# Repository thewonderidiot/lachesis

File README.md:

# Project Lachesis: AGC Core Rope Memory Readers

This repository contains all of the design files for safe, portable Block I and Block II Apollo Guidance Computer (AGC) core rope memory readers. For a detailed explanation of how it all works, check out [CuriousMarc's video featuring this project](https://www.youtube.com/watch?v=hckwxq8rnr0).

*Block 2 reader being used to dump the rope modules flown on Skylab-2 at the New Mexico Museum of Space History*

## Rope Safety Considerations

The rope readers are designed to be electrically and mechanically exactly identical to real AGCs from the point of view of the rope modules. Exact mechanical dimensions and interfacing circuits were copied from the original AGC engineering drawings, obtained from the National Archives. During bringup, all circuits are calibrated to the [original procurement specifications](https://github.com/thewonderidiot/lachesis/tree/main/docs). Connections to the rope modules are made using [replica Malco Mini-Wasp pins generously provided by Samtec](https://www.youtube.com/watch?v=ThOXgcOOA1M).

Additionally:
* A hotswap controller is used to switch all power being applied to the rope module. This controller monitors for overvoltage, undervoltage, and overcurrent, and will automatically cut power to the rope if limits are violated. The enable for this hotswap controller must be actively held high by the microcontroller in the FPGA for rope power to remain enabled.
* The microcontroller is configured with ~95ms watchdog timer. If the software gets stuck, the resulting watchdog reset will take all outputs low, thus cutting power to the rope.
* 250mA fuses have been added to the 450mA power filter circuits. These fuses are capable of withstanding the nominal 1-to-5-microsecond-long 450mA current pulses. However, if a driver gets stuck on for any reason, the associated fuse will blow within approximately 1 second. Calculations by thermal engineer friends suggest that, conservatively, a sustained 450mA on one of the drive wires would only be damaging to the rope module after 30 seconds.

## Block I Rework

The Sense & Driver Board requires a small amount of rework when used in the Block I configuration. While designing the board, I focused on getting Block II correct, while trying not to do anything that would outright prevent Block I compatibility. The only thing I didn't account for in the design is that from the perspective of the sense amplifiers, current on the sense lines actually flows in opposite directions between Block I and Block II. For Block II, the sense amplifiers pull the sense lines up to 14V, and a 128mA current sink is connected to the module select pin. Block I does not yet have this pin; instead, the sense lines were pulled *down* to 3V. Lacking a 3V rail capable of sinking the necessary current, the 128mA module select driver forms a perfectly suitable substitute. This can be accomplished by depopulating F9 and C11, and running a wire from pin A32 of the main connector to the + pad of C11.

## Rope Modules Archived

This is a non-exhaustive list of the rope modules that have been successfully read using the rope readers. Redundant reads of the same software from different physical modules are not listed.

<table>
  <tr>
    <th>Program</th>
    <th width=15%>Rope Part No.</th>
    <th>Source</th>
    <th width="50%">Notes</th>
  </tr>
  <tr>
    <td rowspan="4">Sunrise 69<br/>(Block I System Test)</td>
    <td>1003133-18</td>
    <td rowspan="2">Anonymous collector</td>
    <td rowspan="4">The 1003733-021 and 1003733-071 modules dumped both have one strand with a single bad diode, requiring parity correction.</td>
  </tr>
  <tr>
    <!--Sunrise 69-->
    <td>1003133-19</td>
    <!--Anonymous Collector-->
    <!--notes-->
  </tr>
  <tr>
    <!--Sunrise 69-->
    <td>1003733-021</td>
    <td>Larry McGlynn</td>
    <!--notes-->
  </tr> 
  <tr>
    <!--Sunrise 69-->
    <td>1003733-071</td>
    <td>Anonymous Collector</td>
    <!--notes-->
  </tr>
  <tr>
    <td rowspan="6">Corona 261<br/>(AS-202)</td>
    <td>1003733-171</td>
    <td rowspan="6">Jimmie Loocke</td>
    <td rowspan="6">All six modules were flown on AS-202. These modules contained a variety of failed or failing diodes, requiring parity correction for several strands. Notably, strands 21 and 23 each had 2 bad diodes, requiring the affected bits to be manually teased out by capturing waveforms of the cores flipping in both directions utilizing a differential probe. Additionally, 1003733-221 contained a broken core, resulting in the total loss of 8 words. Fortunately, these words turned out to be identical to the Apollo 4/6 software, Solarium 55.</td>
  </tr>
  <tr>
    <!--Corona 261-->
    <td>1003733-191</td>
    <!--Jimmie Loocke-->
    <!--notes-->
  </tr>
  <tr>
    <!--Corona 261-->
    <td>1003733-211</td>
    <!--Jimmie Loocke-->
    <!--notes-->
  </tr>
  <tr>
    <!--Corona 261-->
    <td>1003733-221</td>
    <!--Jimmie Loocke-->
    <!--notes-->
  </tr>
  <tr>
    <!--Corona 261-->
    <td>1003733-231</td>
    <!--Jimmie Loocke-->
    <!--notes-->
  </tr>
  <tr>
    <!--Corona 261-->
    <td>1003733-241</td>
    <!--Jimmie Loocke-->
    <!--notes-->
  </tr>
  <tr>
    <td rowspan="5">Sunspot ?<br/>(Early Apollo 1 release)</td>
    <td>1003733-251</td>
    <td rowspan="5">Dr. Nick Gessler</td>
    <td rowspan="5">Unfortunately, all modules have many failed diodes, precluding easy software recovery. Work to correct resulting errors is ongoing.</td>
  </tr>
  <tr>
    <!--Sunspot-->
    <td>1003733-261</td>
    <!--Dr. Nick Gessler-->
    <!--notes-->
  </tr>
  <tr>
    <!--Sunspot-->
    <td>1003733-281</td>
    <!--Dr. Nick Gessler-->
    <!--notes-->
  </tr>
  <tr>
    <!--Sunspot-->
    <td>1003733-291</td>
    <!--Dr. Nick Gessler-->
    <!--notes-->
  </tr>
  <tr>
    <!--Sunspot-->
    <td>1003733-311</td>
    <!--Dr. Nick Gessler-->
    <!--notes-->
  </tr>
  <tr>
    <td rowspan="5">Solarium 55<br/>(Apollo 4 and 6)</td>
    <td>1003733-461</td>
    <td rowspan="5">Jimmie Loocke</td>
    <td rowspan="5">All five modules were flown on Apollo 4.</td>
  </tr>
  <tr>
    <!--Solarium 55-->
    <td>1003733-471</td>
    <!--Jimmie Loocke-->
    <!--notes-->
  </tr>
  <tr>
    <!--Solarium 55-->
    <td>1003733-481</td>
    <!--Jimmie Loocke-->
    <!--notes-->
  </tr>
  <tr>
    <!--Solarium 55-->
    <td>1003733-511</td>
    <!--Jimmie Loocke-->
    <!--notes-->
  </tr>
  <tr>
    <!--Solarium 55-->
    <td>1003733-521</td>
    <!--Jimmie Loocke-->
    <!--notes-->
  </tr>
  <tr>
    <td>Aurora 85<br/>(Initial LM System Test)</td>
    <td>2003053-071</td>
    <td>Anonymous Collector</td>
    <td>Module B2 from Aurora 85. While module B1 of Aurora 88 is equivalent to Aurora 85, module B3 is not, so Aurora 85 has not yet been fully recovered.</td>
  </tr>
  <tr>
    <td rowspan="3">Aurora 88<br/>(Final LM System Test)</td>
    <td>2003972-011</td>
    <td rowspan="3">Steve Jurvetson</td>
    <td rowspan="3">Rope modules were installed in the guidance pallet flown on the F-8 in the Digital Fly-By-Wire program. The whereabouts of the actual DFBW modules are unknown.</td>
  </tr>
  <tr>
    <!--Aurora 88-->
    <td>2003972-091</td>
    <!--Steve Jurvetson-->
    <!--notes-->
  </tr>
  <tr>
    <!--Aurora 88-->
    <td>2003972-111</td>
    <!--Steve Jurvetson-->
    <!--notes-->
  </tr>
  <tr>
    <td>Sundial B<br/>(Initial CM System Test)</td>
    <td>2003053-151</td>
    <td>Anonymous Collector</td>
    <td>Module B2 from Sundial B. While module B1 of Sundial B is equivalent to Sundial D, module B3 is not, so Sundial B has not yet been fully recovered.</td>
  </tr>
  <tr>
    <td rowspan="2">Colossus 237<br/>(Apollo 8)</td>
    <td>2003972-541</td>
    <td rowspan="2">Anonymous Collector</td>
    <td rowspan="2">2003972-541 is marked "SCRAP UNIT" in red, but read without errors.</td>
  </tr>
  <tr>
    <!--Colossus 237-->
    <td>2003972-571</td>
    <!--Anonymous Collector-->
    <!--notes-->
  </tr>
  <tr>
    <td>Luminary 69<br/>(Apollo 10 LM)</td>
    <td>2003972-751</td>
    <td>Anonymous Collector</td>
    <td>First rope module successfully dumped.</td>
  </tr>
  <tr>
    <td rowspan="6">Comanche 67<br/>(Apollo 12 CM)</td>
    <td>2003972-1081</td>
    <td rowspan="6">Anonymous Collector</td>
    <td rowspan="6">Modules B1 through B4 were part of the flight spare set for Apollo 12. The high serial numbers for modules B5 and B6 suggest they were manufactured after the flight, for unknown reasons.</td>
  </tr>
  <tr>
    <!--Comanche 67-->
    <td>2003972-1091</td>
    <!--Anonymous Collector-->
    <!--notes-->
  </tr>
  <tr>
    <!--Comanche 67-->
    <td>2003972-1111</td>
    <!--Anonymous Collector-->
    <!--notes-->
  </tr>
  <tr>
    <!--Comanche 67-->
    <td>2003972-1121</td>
    <!--Anonymous Collector-->
    <!--notes-->
  </tr>
  <tr>
    <!--Comanche 67-->
    <td>2003972-1131</td>
    <!--Anonymous Collector-->
    <!--notes-->
  </tr>
  <tr>
    <!--Comanche 67-->
    <td>2003972-1141</td>
    <!--Anonymous Collector-->
    <!--notes-->
  </tr>
  <tr>
    <td>Comanche 72<br/>(Initial Apollo 13 CM release)</td>
    <td>2010802-021</td>
    <td>Anonymous Collector</td>
    <td>Module was initially slated fly on Apollo 13, but a bugfix in response to the Apollo 12 lightning strike requiring a re-release resulted in it remaining grounded.</td>
  </tr>
  <tr>
    <td>LM131 rev 1<br/>(Final Apollo 13 LM release)</td>
    <td>2010802-121</td>
    <td>Anonymous Collector</td>
    <td>Flight spare module. This is the only module different between LM131 rev 1 and Luminary 131 (for which scans of a program listing are available), so recovery of the software from this module resulted in the complete recovery of LM131 rev 1.</td>
  </tr>
  <tr>
    <td rowspan="6">Skylark 48<br/>(Skylab and ASTP CM)</td>
    <td>2010802-541</td>
    <td rowspan="6">New Mexico Museum of Space History</td>
    <td rowspan="6">All six modules were flown on the Skylab-2 mission, and possibly reflown on a later mission. Made possible by Chris Orwoll and Larry McGlynn.</td>
  </tr>
  <tr>
    <!--Skylark 48-->
    <td>2010802-551</td>
    <!--New Mexico Museum of Space History-->
    <!--notes-->
  </tr>
  <tr>
    <!--Skylark 48-->
    <td>2010802-561</td>
    <!--New Mexico Museum of Space History-->
    <!--notes-->
  </tr>
  <tr>
    <!--Skylark 48-->
    <td>2010802-571</td>
    <!--New Mexico Museum of Space History-->
    <!--notes-->
  </tr>
  <tr>
    <!--Skylark 48-->
    <td>2010802-581</td>
    <!--New Mexico Museum of Space History-->
    <!--notes-->
  </tr>
  <tr>
    <!--Skylark 48-->
    <td>2010802-591</td>
    <!--New Mexico Museum of Space History-->
    <!--notes-->
  </tr>
</table>

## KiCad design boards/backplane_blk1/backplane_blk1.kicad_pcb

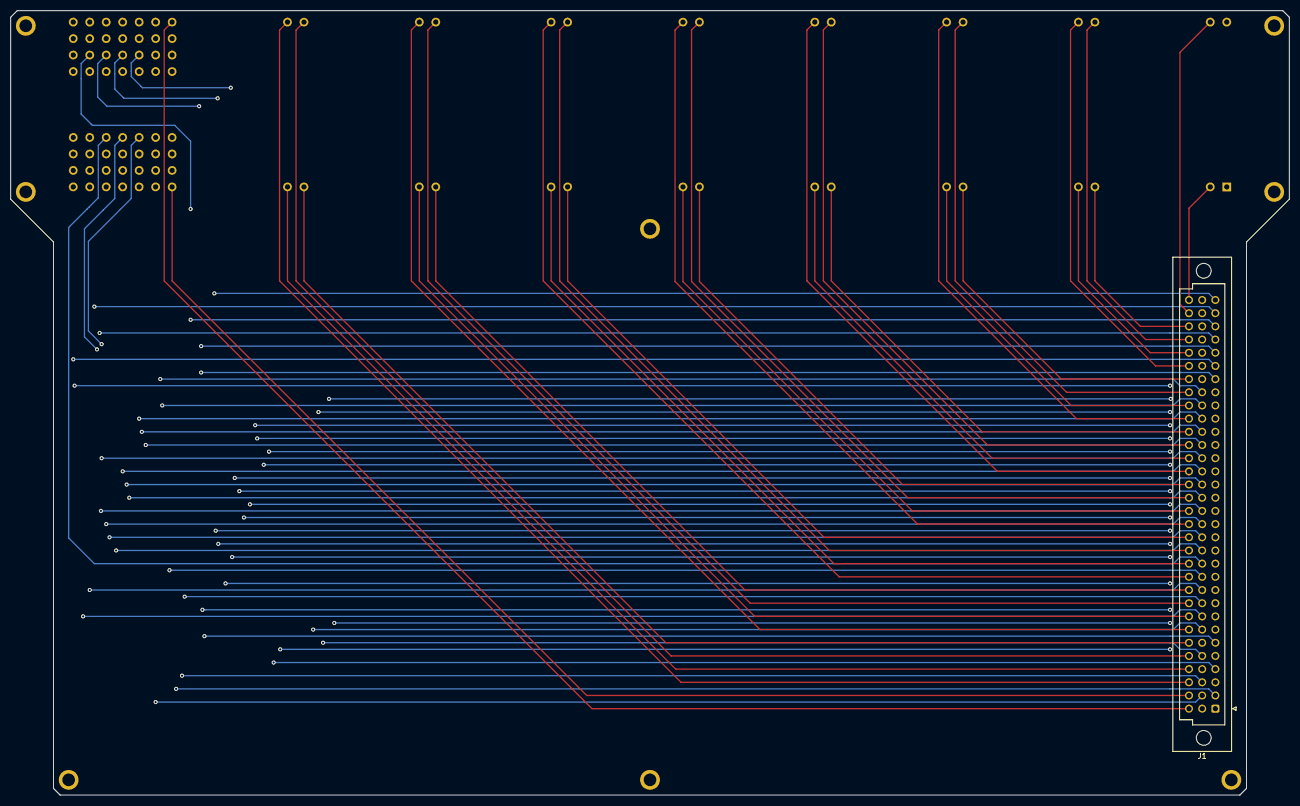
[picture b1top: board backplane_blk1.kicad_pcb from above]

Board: 4 copper layers, 246.4 x 151.1 mm, 10 parts (0 on the bottom side), 83 nets.

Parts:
H1, H2, H3, H4, H5, H6, H7, H8: MountingHole_Pad; MountingHole_No2_Pad
J1: DIN41612_03x32_C; DIN41612_R_3x32_Male_Vertical_THT
J2: Conn_04x22; Block1_Connector

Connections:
/GAR01: J1.c30, J2.5
/GAR02: J1.c28, J2.7
/GAR03: J1.c26, J2.9
/GAR04: J1.c24, J2.11
/GAR05: J1.c22, J2.13
/GAR06: J1.c20, J2.15
/GAR07: J1.c18, J2.17
/GAR08: J1.c16, J2.19
/GAR09: J1.c14, J2.21
/GAR10: J1.c12, J2.23
/GAR11: J1.c10, J2.25
/GAR12: J1.c8, J2.27
/GAR13: J1.c6, J2.29
/GAR14: J1.c4, J2.31
/GAR15: J1.c32, J2.3
/GAR16: J1.c2, J2.33
/GBR01: J1.c29, J2.6
/GBR02: J1.c27, J2.8
/GBR03: J1.c25, J2.10
/GBR04: J1.c23, J2.12
/GBR05: J1.c21, J2.14
/GBR06: J1.c19, J2.16
/GBR07: J1.c17, J2.18
/GBR08: J1.c15, J2.20
/GBR09: J1.c13, J2.22
/GBR10: J1.c11, J2.24
/GBR11: J1.c9, J2.26
/GBR12: J1.c7, J2.28
/GBR13: J1.c5, J2.30
/GBR14: J1.c3, J2.32
/GBR15: J1.c31, J2.4
/GBR16: J1.c1, J2.40
/R01CD: J1.b12, J2.68
/R01FD: J1.b13, J2.67
/R02CD: J1.b14, J2.66
/R02FD: J1.b15, J2.65
/R03CD: J1.b16, J2.60
/R03FD: J1.b17, J2.59
/R04CD: J1.b18, J2.58
/R04FD: J1.b19, J2.57
/R05CD: J1.b20, J2.52
/R05FD: J1.b21, J2.51
/R06CD: J1.b22, J2.50
/R06FD: J1.b23, J2.49
/R07CD: J1.b24, J2.43
/R07FD: J1.b25, J2.42
/RPCD: J1.b8, J2.74
/RPFD: J1.b10, J2.73
/RSTR1D: J1.b2, J2.41
/SDR00: J1.b11, J2.34
/SDR01: J1.a2, J2.35
/SDR02: J1.b9, J2.36
/SDR03: J1.b3, J2.44
/SDR04: J1.b7, J2.45
/SDR05: J1.a5, J2.37
/SDR06: J1.b5, J2.38
/SDR07: J1.a7, J2.39
/SETARN: J1.a29, J2.76
/SETBRN: J1.a25, J2.82
/SETCRN: J1.a32, J2.77
/SETDRN: J1.a28, J2.87
/X01CN: J1.a10, J2.69
/X01FN: J1.a12, J2.70
/X02CN: J1.a13, J2.71
/X02FN: J1.a14, J2.72
/X03CN: J1.a15, J2.61
/X03FN: J1.a16, J2.62
/X04CN: J1.a17, J2.63
/X04FN: J1.a18, J2.64
/X05CN: J1.a19, J2.53
/X05FN: J1.a20, J2.54
/X06CN: J1.a21, J2.55
/X06FN: J1.a22, J2.56
/X07CN: J1.a23, J2.46
/X07FN: J1.a24, J2.47
/XPCN: J1.a6, J2.79
/XPFN: J1.a8, J2.80
/XRST1N: J1.a4, J2.48
/XSETAD: J1.a31, J2.75
/XSETBD: J1.a27, J2.81
/XSETCD: J1.a30, J2.78
/XSETDD: J1.a26, J2.88
GND: H1.1, H2.1, H3.1, H4.1, H5.1, H6.1, H7.1, H8.1, J1.b26, J1.b27, J1.b28, J1.b29, J1.b30, J1.b31, J1.b32

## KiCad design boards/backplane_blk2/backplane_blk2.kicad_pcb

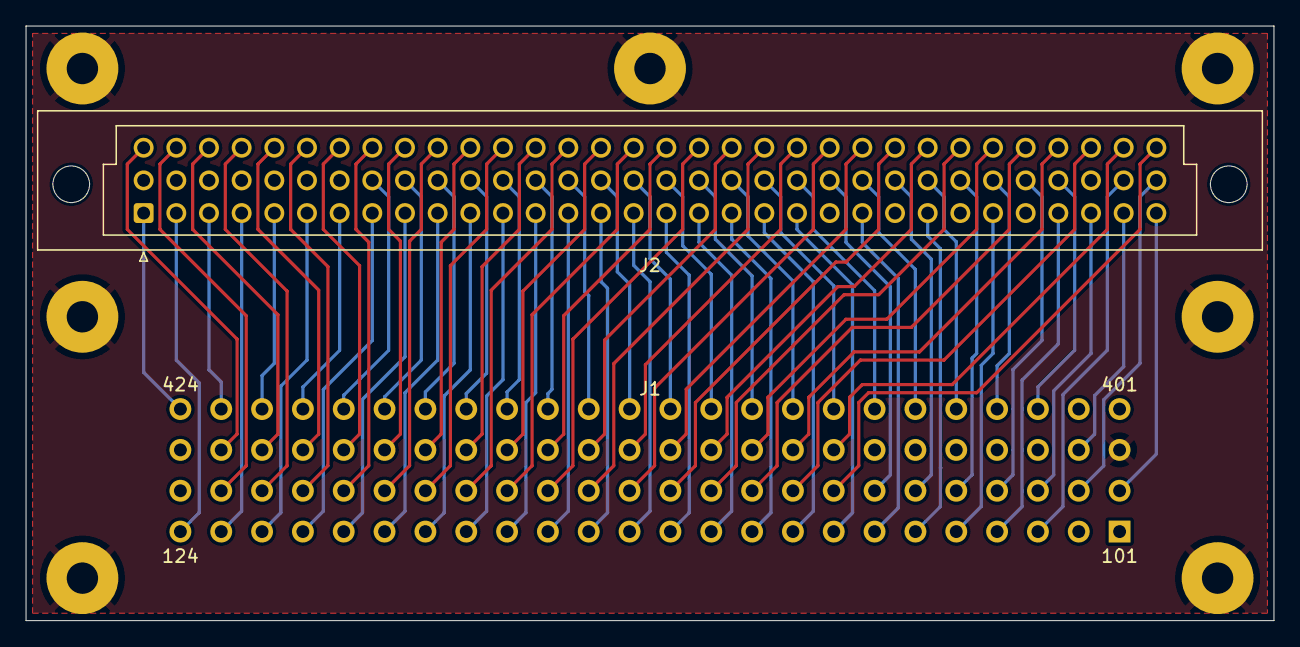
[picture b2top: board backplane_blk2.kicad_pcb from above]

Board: 4 copper layers, 97.0 x 46.2 mm, 9 parts (0 on the bottom side), 90 nets.

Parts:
H1, H2, H3, H4, H5, H6, H7: MountingHole_Pad; MountingHole_No2_0.22in_Pad
J1: Conn_04x24; Rope_Connector
J2: DIN41612_03x32_C; DIN41612_C_3x32_Female_Vertical_THT

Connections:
/GAR01: J1.322, J2.c3
/GAR02: J1.321, J2.c5
/GAR03: J1.320, J2.c7
/GAR04: J1.319, J2.c9
/GAR05: J1.318, J2.c11
/GAR06: J1.317, J2.c13
/GAR07: J1.316, J2.c15
/GAR08: J1.315, J2.c17
/GAR09: J1.314, J2.c19
/GAR10: J1.313, J2.c21
/GAR11: J1.312, J2.c23
/GAR12: J1.311, J2.c25
/GAR13: J1.310, J2.c27
/GAR14: J1.309, J2.c29
/GAR15: J1.323, J2.c1
/GAR16: J1.308, J2.c31
/GBR01: J1.222, J2.c4
/GBR02: J1.221, J2.c6
/GBR03: J1.220, J2.c8
/GBR04: J1.219, J2.c10
/GBR05: J1.218, J2.c12
/GBR06: J1.217, J2.c14
/GBR07: J1.216, J2.c16
/GBR08: J1.215, J2.c18
/GBR09: J1.214, J2.c20
/GBR10: J1.213, J2.c22
/GBR11: J1.212, J2.c24
/GBR12: J1.211, J2.c26
/GBR13: J1.210, J2.c28
/GBR14: J1.209, J2.c30
/GBR15: J1.223, J2.c2
/GBR16: J1.208, J2.c32
/MODR1: J1.201, J2.a32
/R01CD: J1.407, J2.b21
/R01FD: J1.408, J2.b20
/R02CD: J1.409, J2.b19
/R02FD: J1.410, J2.b18
/R03CD: J1.411, J2.b17
/R03FD: J1.412, J2.b16
/R04CD: J1.413, J2.b15
/R04FD: J1.414, J2.b14
/R05CD: J1.415, J2.b13
/R05FD: J1.416, J2.b12
/R06CD: J1.417, J2.b11
/R06FD: J1.418, J2.b10
/R07CD: J1.419, J2.b9
/R07FD: J1.420, J2.b8
/RPCD: J1.405, J2.b25
/RPFD: J1.406, J2.b23
/RSTRAD: J1.123, J2.a4
/RSTRBD: J1.121, J2.a8
/RSTRCD: J1.424, J2.a1
/RSTRDD: J1.422, J2.a5
/SETARN: J1.103, J2.b31
/SETCRN: J1.404, J2.b27
/STR01: J1.207, J2.b22
/STR02: J1.302, J2.a31
/STR03: J1.206, J2.b24
/STR04: J1.303, J2.b30
/STR05: J1.205, J2.b26
/STR06: J1.304, J2.a28
/STR07: J1.204, J2.b28
/STR08: J1.305, J2.a26
/STR09: J1.203, J2.a30
/STR10: J1.306, J2.a24
/STR11: J1.202, J2.b32
/STR12: J1.307, J2.a22
/X01CN: J1.107, J2.a23
/X01FN: J1.108, J2.a21
/X02CN: J1.109, J2.a20
/X02FN: J1.110, J2.a19
/X03CN: J1.111, J2.a18
/X03FN: J1.112, J2.a17
/X04CN: J1.113, J2.a16
/X04FN: J1.114, J2.a15
/X05CN: J1.115, J2.a14
/X05FN: J1.116, J2.a13
/X06CN: J1.117, J2.a12
/X06FN: J1.118, J2.a11
/X07CN: J1.119, J2.a10
/X07FN: J1.120, J2.a9
/XPCN: J1.105, J2.a27
/XPFN: J1.106, J2.a25
/XRSTAN: J1.124, J2.a2
/XRSTBN: J1.122, J2.a6
/XRSTCN: J1.423, J2.a3
/XRSTDN: J1.421, J2.a7
/XSETAB: J1.104, J2.a29
/XSETCD: J1.403, J2.b29
GND: H1.1, H2.1, H3.1, H4.1, H5.1, H6.1, H7.1, J1.301, J2.b1, J2.b2, J2.b3, J2.b4, J2.b5, J2.b6, J2.b7
